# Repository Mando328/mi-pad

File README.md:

# mi-pad

A small macropad bulit with QMK in colaboration with Hackclub

The hardware part was pretty easy for me, but writing the firmware using QMK proved to me that i am very bad at software lol, i mainly used copilot to write it for me.
Below you can see images of my bulid, and when I will asemble it, I will add photos of finished version.
It has very minimalistic desing with no addons, just keys and an encoder, no lights or glitter included.

List of parts:
-Seeed XIAO RP2040
-9x MX-Style switches
-EC11 Rotary encoder
-M3x16mm screws
-M3x5mx4mm heatset inserts
-Blank DSA keycaps (White)
-3D printed case printed on Bambu Lab A1

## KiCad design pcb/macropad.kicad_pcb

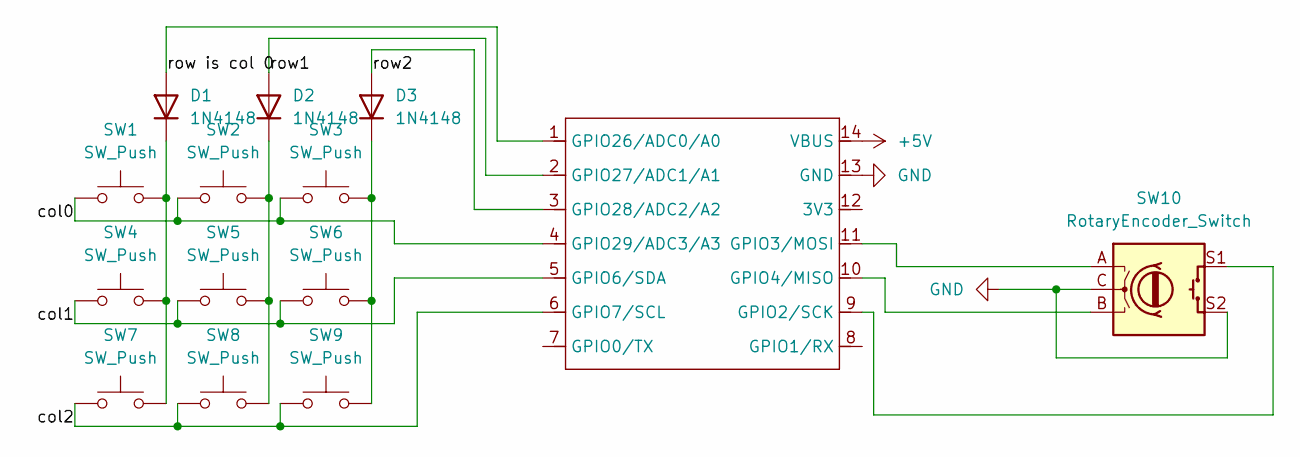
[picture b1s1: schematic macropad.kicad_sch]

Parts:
D1, D2, D3: 1N4148; D_DO-35_SOD27_P7.62mm_Horizontal
SW1, SW2, SW3, SW4, SW5, SW6, SW7, SW8, SW9: SW_Push; SW_Cherry_MX_1.00u_PCB
SW10: RotaryEncoder_Switch; RotaryEncoder_Alps_EC11E-Switch_Vertical_H20mm
U1: XIAO-RP2040-DIP

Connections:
+5V: U1.14 (VBUS)
/COL0: D1.2 (A), U1.1 (GPIO26/ADC0/A0)
/COL1: D2.2 (A), U1.2 (GPIO27/ADC1/A1)
/COL2: D3.2 (A), U1.3 (GPIO28/ADC2/A2)
/ROW0: SW1.1, SW2.1, SW3.1, U1.4 (GPIO29/ADC3/A3)
/ROW1: SW4.1, SW5.1, SW6.1, U1.5 (GPIO6/SDA)
/ROW2: SW7.1, SW8.1, SW9.1, U1.6 (GPIO7/SCL)
GND: SW10.C, SW10.S2, U1.13 (GND)
unnamed: D1.1 (K), SW1.2, SW4.2, SW7.2
unnamed: D2.1 (K), SW2.2, SW5.2, SW8.2
unnamed: D3.1 (K), SW3.2, SW6.2, SW9.2
unnamed: SW10.S1, U1.9 (GPIO2/SCK)
unnamed: SW10.A, U1.11 (GPIO3/MOSI)
unnamed: SW10.B, U1.10 (GPIO4/MISO)

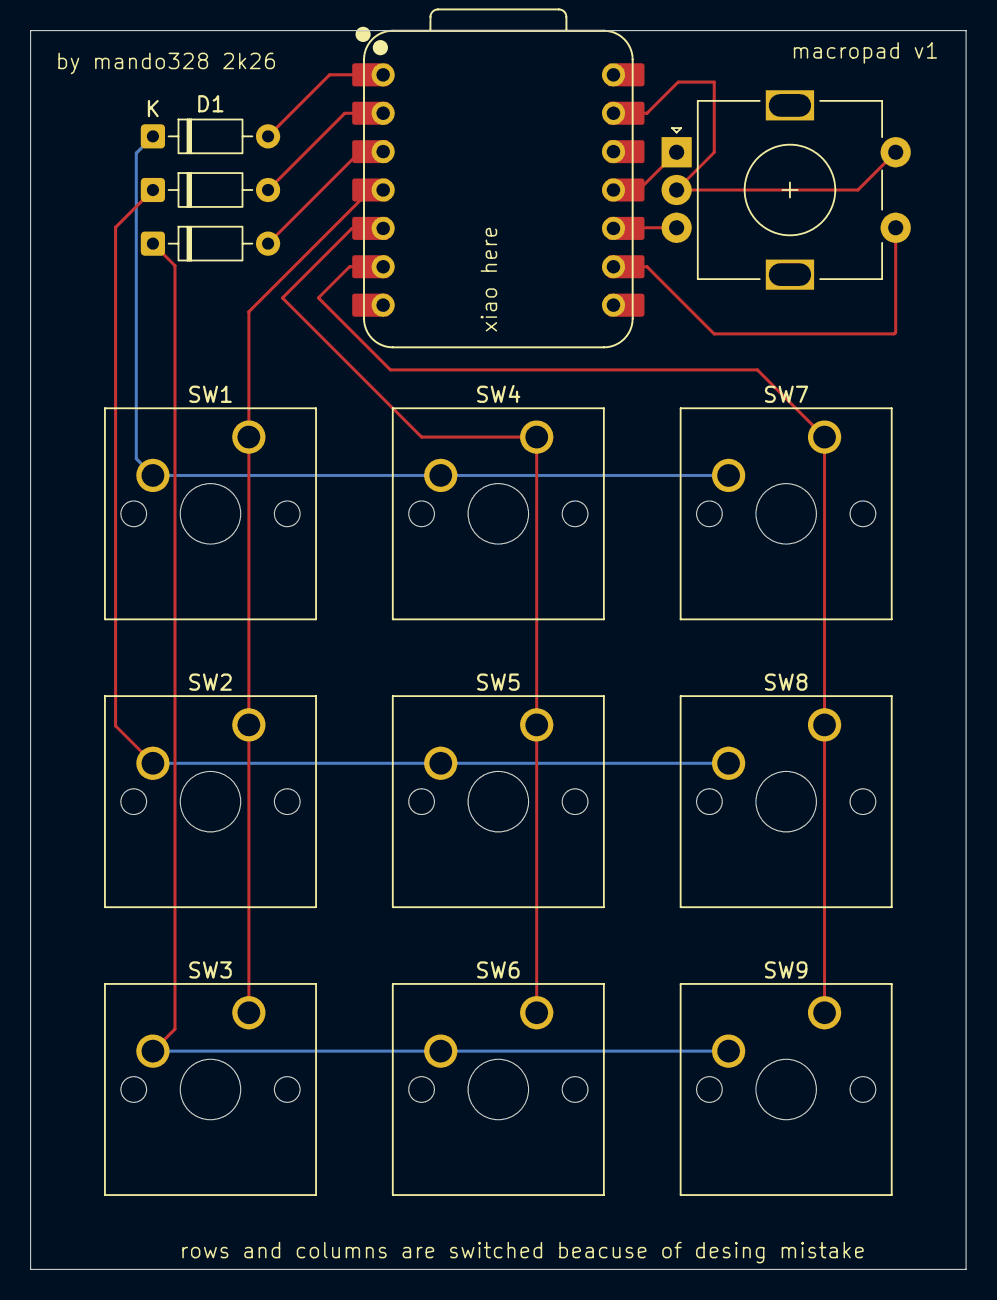
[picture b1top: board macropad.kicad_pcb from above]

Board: 2 copper layers, 61.9 x 82.0 mm, 14 parts (0 on the bottom side), 13 nets.

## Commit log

2026-01-11 Enhance README with details and images of the build
    Expanded the README with personal insights and images.
2026-01-11 Revise README with Copilot usage note
    Updated README to include mention of using Copilot for firmware development.
2026-01-11 Stl and PCB files
2026-01-11 Include parts list in README
    Added a list of parts used in the project.
2026-01-11 Firmware files added
2026-01-12 added more pcb files
2026-01-12 step files added
2026-01-12 Added render
2026-01-12 Update to structure
2026-01-13 added every single possible pcb file
